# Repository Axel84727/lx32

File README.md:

# lx32

I built a computer from scratch because ChatGPT told me "no hay huevos." So here we are.

Custom processor, custom PCB, custom compiler. The whole thing.

---

## ok first let me flex

Zero violations. Zero unconnected items. I cried a little.

(also this is the 5th time I rewrote this README. if it still looks AI-generated I give up)

---

## what is this actually

lx32 is a 32-bit CPU with a custom instruction set, running on a custom PCB, compiled by a custom LLVM backend. You can write C, compile it, and it runs on this thing.

I wanted to actually understand how computers work, not just read about it. So I built one.

The board is 80x60mm, about the size of a credit card. Black soldermask, gold finish.

---

## the board

Here's what it looks like:

The schematics:

Measurements:

Long:

Width:

Full view:

The main chip is a Lattice iCE40HX4K FPGA — that's what becomes the processor. I chose it because the toolchain is fully open source (Yosys, nextpnr, icepack).

The rest of the board is USB-C for power and programming, SPI flash so the bitstream loads on power-up, two LDOs for the separate 3.3V and 1.2V rails, a USB-UART bridge to talk to it from my laptop, 32KB of external SRAM, and a VGA header. There's also an OLED that shows register values and the current instruction live, which is the coolest part honestly.

3D render, front:

3D render, back:

`.STEP` file if you want it: [`lx32-fpga.step`](./cad/lx32-fpga.step)

---

## the processor

32 registers, fixed 32-bit instruction width, single-cycle. I made up the instruction encoding: ADD, SUB, AND, OR, XOR, shifts, loads, stores, branches, jumps, LUI, AUIPC. x0 is hardwired to zero. Everything is in `rtl/` and every module has a spec in `docs/rtl/`.

---

## how I know it works

I wrote a Rust model of the processor, then a fuzzer that fires random instruction sequences through both Verilator and the model at the same time and compares cycle by cycle.

| module | test vectors | result |
|---|---|---|
| ALU | 100,000,000 | passed |
| Branch Unit | 100,000,000 | passed |
| Control Unit | 100,000,000 | passed |
| Register File | 100,000,000 | passed |
| Full System | 100,000,000 | passed |
| **Total** | **1,100,000,000+** | **zero failures** |

Runs in under 75 seconds. I also tortured my laptop with a Python script to run it on loop. There are Coq proofs for some properties and formal verification through sby too.

---

## the compiler

LLVM backend for lx32 — instruction patterns, register file, calling convention. Eight programs compile and run end-to-end: return, pointer store, call chain, branch/loop, compare/assign, pointer walk, iterative fibonacci, recursive fibonacci.

Write C, compile with LLVM, runs on this board.

---

## the gold art

ENIG means the exposed copper comes out gold on black soldermask. I put personal stuff on both sides.

The back has an infinity symbol, *pototo ralora arerita*, *"All we need is love"*, `Lizzie <3`, `22/03/09`, and `67` (that last one I didn't choose, it just ended up there).

It's a working computer and it also has my whole heart on it.

---

## run it yourself

```bash
git clone https://github.com/Axel84727/lx32.git
cd lx32
make setup
```

You'll need: `verilator`, Rust (`cargo`), `coqc`, `sby`, `yosys`, `z3`, `g++`.

```bash
make sim TB=lx32_system_tb    # full system sim
make validate                  # full test suite (1.1B vectors)
make formal-all                # formal proofs
```

---

## BOM

Full BOM: [`lx32-bom.csv`](./lx32-bom.csv)

| Part | Qty | Total |
| :--- | :---: | ---: |
| Custom LX32 PCB (JLCPCB, 4-layer, ENIG, black mask) | 5 | $15.00 |
| Lattice iCE40HX4K-TQ144 | 2 | $19.00 |
| CH340C USB-UART (SOP-16) | 2 | $0.90 |
| W25Q32JVSSIQ SPI Flash 32Mb | 2 | $1.10 |
| AP2112K-3.3TRG1 LDO 3.3V | 2 | $0.60 |
| AP2112K-1.2TRG1 LDO 1.2V | 2 | $0.60 |
| 25MHz Crystal SMD 3225 | 2 | $0.70 |
| USB-C connector SMD | 2 | $0.80 |
| Microchip 23K256 SPI SRAM (SOIC-8) | 2 | $1.20 |
| VGA 2x5 header + 68Ω resistors | -- | $0.76 |
| Passives (caps, resistors, LEDs) | -- | $0.58 |
| 2.54mm pin headers | 1 | $0.80 |
| M3 standoffs + screws | 12 | $1.00 |
| 0.96" OLED display | 1 | $14.22 |
| Jumper wires + breadboard | 1 | $9.89 |
| Shipping JLCPCB to Uruguay | -- | $22.00 |
| Shipping Tiendamia | -- | $38.00 |
| **Total** | | **$127.15** |

---

MIT

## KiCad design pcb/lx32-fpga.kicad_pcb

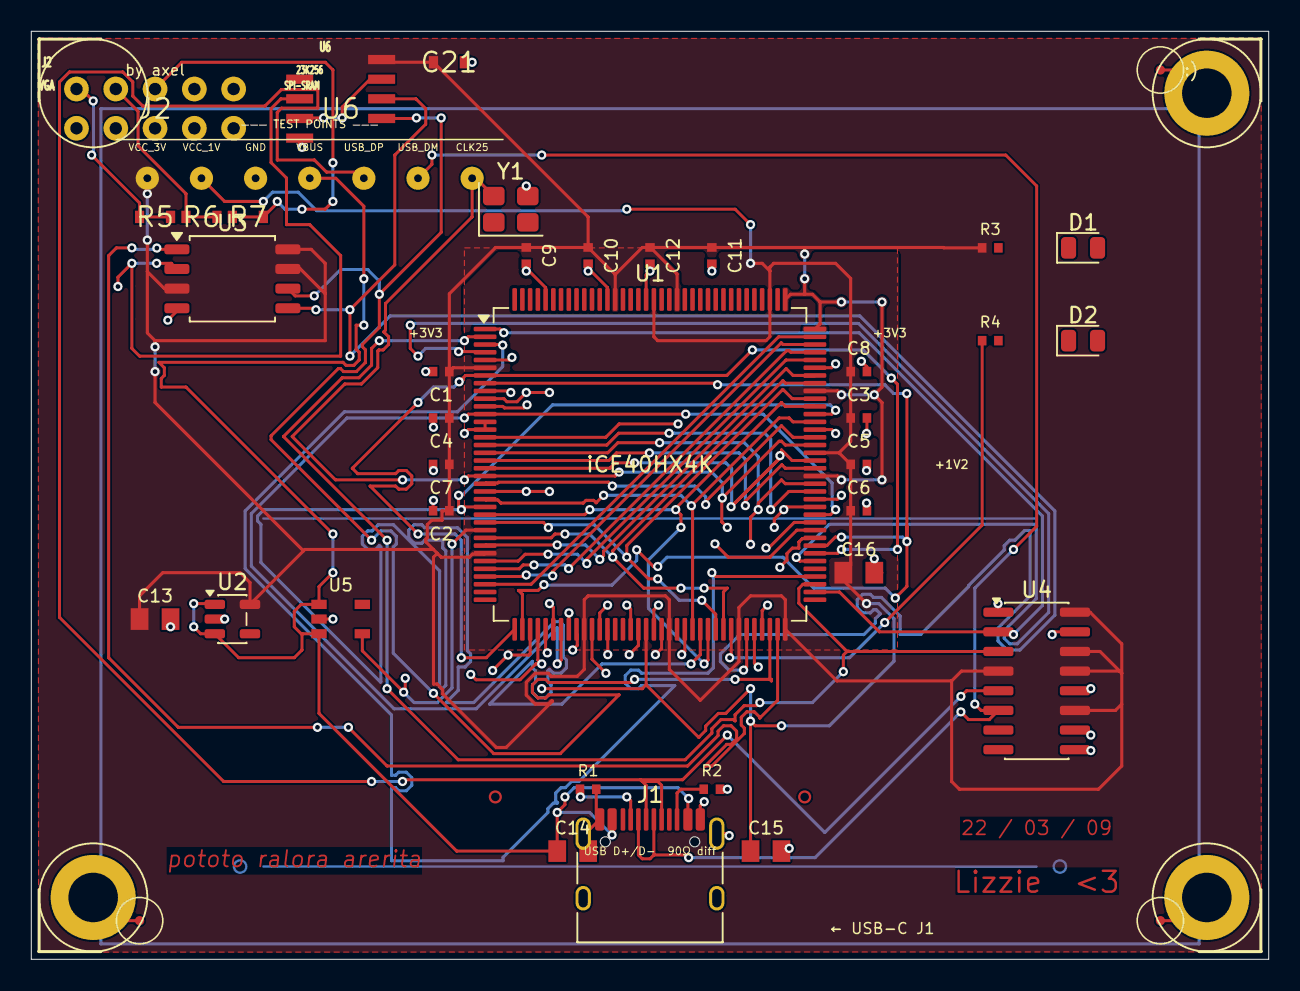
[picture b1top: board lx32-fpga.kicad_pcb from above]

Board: 4 copper layers, 80.0 x 60.0 mm, 49 parts (0 on the bottom side), 45 nets.

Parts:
C1, C2, C3, C4, C5, C6, C7, C8, C9, C10, C11, C12: 100nF; C_0402_1005Metric
C13, C14, C15, C16: 10uF; C_0805_2012Metric
C21: 100nF
D1, D2: LED; LED_0805_2012Metric
FID1, FID2, FID3: Fiducial
J1: USB_C_Receptacle_USB2.0_14P; USB_C_Receptacle
J2: VGA_HDR
MH1, MH2, MH3, MH4: MH_M3
R1, R2: 5.1k; R_0402_1005Metric
R3, R4: 100R; R_0402_1005Metric
R5, R6, R7: 68R
TP1: VCC_3V3
TP2: VCC_1V2
TP3: GND
TP4: VBUS
TP5: USB_DP
TP6: USB_DM
TP7: CLK25
U1: ICE40HX4K-TQ144; TQFP-144_20x20mm_P0.5mm
U2: AP2112K-3.3; SOT-23-5
U3: W25Q32JVSS; SOIC-8_5.3x5.3mm_P1.27mm
U4: CH340C; SOIC-16_3.9x9.9mm_P1.27mm
U5: AP2112K-1.2; SOT-23-5
U6: 23K256
Y1: Crystal; Crystal_SMD_3225-4Pin

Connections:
CC1: J1.A5 (CC1), R1.1
CC2: J1.B5 (CC2), R2.1
CDONE: R4.1, U1.65 (CDONE)
CLK25: TP7.1, U1.20 (IOL_13B_GBIN7), U1.52 (IOB_82_GBIN4), U1.93 (IOR_140_GBIN3), Y1.4
GND: C1.2, C2.2, C3.2, C4.2, C5.2, C6.2, C7.2, C8.2, C9.2, C10.2, C11.2, C12.2, C13.2, C14.2, C15.2, C16.2, C21.2, FID1.1, FID2.1, J1.A1 (GND), J1.A12 (GND), J1.B1 (GND), J1.B12 (GND), J1.SH (SHIELD), J2.6, J2.7, J2.8, J2.9, J2.10, MH2.1, MH3.1, MH4.1, R1.2, R2.2, TP3.1, U1.5 (GND), U1.13 (GND), U1.14 (GND), U1.53 (GNDPLL0), U1.59 (GND), U1.69 (GND), U1.86 (GND), U1.103 (GND), U1.127 (GNDPLL1), U1.132 (GND), U1.140 (GND), U2.2 (GND), U3.4 (GND), U4.1 (GND), U4.9 (~CTS), U4.10 (~DSR), U4.12 (~DCD), U4.15 (R232), U5.2, U6.4, Y1.3
unnamed: U1.3 (IOL_3A), U1.76 (IOR_112)
unnamed: U1.4 (IOL_3B), U1.78 (IOR_114)
unnamed: U1.7 (IOL_4A), U1.37 (IOB_56), U1.79 (IOR_115)
unnamed: U1.8 (IOL_4B), U1.38 (IOB_57), U1.80 (IOR_116)
unnamed: U1.9 (IOL_5A), U1.39 (IOB_61), U1.81 (IOR_117)
unnamed: U1.10 (IOL_5B), U1.41 (IOB_63), U1.82 (IOR_118)
unnamed: U1.11 (IOL_8A), U1.42 (IOB_64), U1.83 (IOR_119)
unnamed: U1.12 (IOL_8B), U1.43 (IOB_71), U1.84 (IOR_120)
unnamed: U1.15 (IOL_10A), U1.44 (IOB_72), U1.85 (IOR_128)
unnamed: U1.16 (IOL_10B), U1.45 (IOB_73), U1.87 (IOR_136)
unnamed: U1.17 (IOL_12A), U1.47 (IOB_79), U1.88 (IOR_137)
unnamed: U1.18 (IOL_12B), U1.48 (IOB_80), U1.90 (IOR_138)
unnamed: U1.19 (IOL_13A), U1.49 (IOB_81_GBIN5), U1.91 (IOR_139)
unnamed: U1.21 (IOL_14A_GBIN6), U1.55 (IOB_91), U1.94 (IOR_141_GBIN2)
unnamed: U1.22 (IOL_14B), U1.56 (IOB_94), U1.95 (IOR_144)
unnamed: U1.23 (IOL_17A), U1.60 (IOB_95), U1.96 (IOR_146)
unnamed: U1.24 (IOL_17B), U1.61 (IOB_96), U1.97 (IOR_147)
unnamed: U1.25 (IOL_18A), U1.62 (IOB_102), U1.98 (IOR_148)
unnamed: U1.26 (IOL_18B), U1.63 (IOB_103_CBSEL0), U1.99 (IOR_152)
unnamed: U1.28 (IOL_23A), U1.64 (IOB_104_CBSEL1), U1.101 (IOR_160)
unnamed: U1.29 (IOL_23B), U1.102 (IOR_161)
unnamed: U1.31 (IOL_24A), U1.104 (IOR_164)
unnamed: U1.32 (IOL_24B), U1.105 (IOR_165)
unnamed: U1.33 (IOL_25A), U1.106 (IOR_166)
unnamed: U1.34 (IOL_25B), U1.107 (IOR_167)
SPI_CLK: U1.70 (IOB_107_SCK), U3.6 (CLK), U6.5
SPI_MISO: U1.68 (IOB_106_SDI), U3.2 (DO/IO_{1}), U6.2
SPI_MOSI: U1.67 (IOB_105_SDO), U3.5 (DI/IO_{0}), U6.6
SPI_SS: U1.71 (IOB_108_SS), U3.1 (~CS)
SRAM_HOLD: U6.3, U6.7
UART_RX: U1.2 (IOL_2B), U1.75 (IOR_111), U4.3 (RXD)
UART_TX: U1.1 (IOL_2A), U1.74 (IOR_110), U4.2 (TXD)
USB_DM: J1.A7 (D-), J1.B7 (D-), TP6.1, U4.6 (UD-)
USB_DP: J1.A6 (D+), J1.B6 (D+), TP5.1, U4.5 (UD+)
VBUS: C14.1, J1.A4 (VBUS), J1.A9 (VBUS), J1.B4 (VBUS), J1.B9 (VBUS), TP4.1, U2.1 (VIN), U2.3 (EN), U5.1, U5.3
VCC_1V2: C3.1, C5.1, C6.1, C8.1, C15.1, C16.1, TP2.1, U1.27 (VCC), U1.40 (VCC), U1.54 (VCCPLL0), U1.92 (VCC), U1.111 (VCC), U1.126 (VCCPLL1), U5.5
VCC_3V3: C1.1, C2.1, C4.1, C7.1, C9.1, C10.1, C11.1, C12.1, C13.1, C21.1, R3.1, TP1.1, U1.6 (VCCIO_3), U1.30 (VCCIO_3), U1.46 (VCCIO_2), U1.57 (VCCIO_2), U1.66 (~CRESET), U1.72 (VCC_SPI), U1.89 (VCCIO_1), U1.100 (VCCIO_1), U1.108 (VPP_2V5), U1.109 (VPP_FAST), U1.123 (VCCIO_0), U1.131 (VCCIO_0), U2.5 (VOUT), U3.3 (~WP/IO_{2}), U3.7 (~HOLD/~RESET/IO_{3}), U3.8 (VCC), U4.4 (V3), U4.11 (~RI), U4.13 (~DTR), U4.14 (~RTS), U4.16 (VCC), U6.8
VGA_B: J2.3, R7.1, R7.2
VGA_G: J2.2, R6.1, R6.2
VGA_R: J2.1, R5.1, R5.2

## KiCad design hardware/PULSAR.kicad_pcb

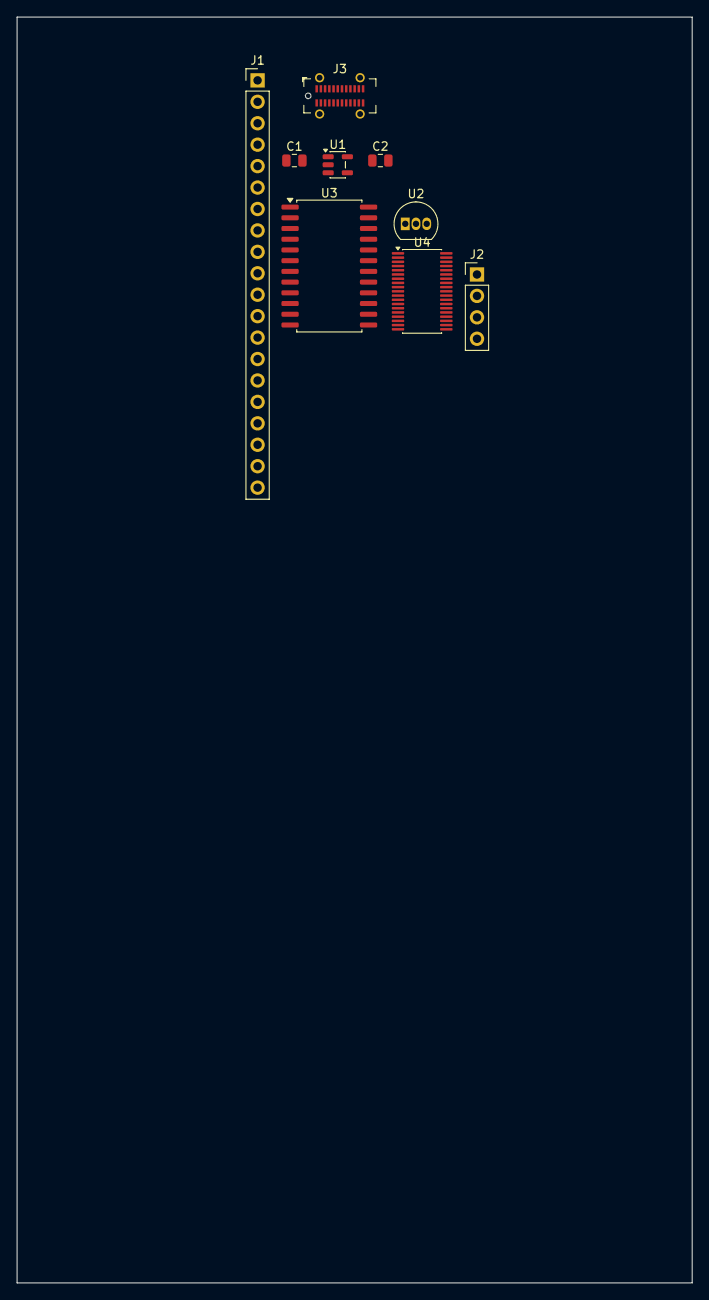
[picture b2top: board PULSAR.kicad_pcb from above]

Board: 4 copper layers, 80.0 x 150.0 mm, 9 parts (0 on the bottom side), 15 nets, no tracks yet.

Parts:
C1, C2: 1uF; C_0805_2012Metric
J1: Conn_01x20; PinHeader_1x20_P2.54mm_Vertical
J2: Conn_01x04; PinHeader_1x04_P2.54mm_Vertical
J3: USB_C_Receptacle; USB_C_Receptacle_GCT_USB4115-03-C
U1: AP2112K-3.3; SOT-23-5
U2: SS49E; TO-92_Inline
U3: CD74HC4067M; SOIC-24W_7.5x15.4mm_P1.27mm
U4: ADS8688; TSSOP-38_4.4x9.7mm_P0.5mm

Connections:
+3.3V: C2.1, J1.1, J2.1, U1.5 (VOUT), U2.1, U3.24 (VCC), U4.2 (~RST/PD), U4.4 (~REFSEL), U4.9 (AVDD), U4.30 (AVDD), U4.34 (DVDD)
+5V: C1.1, J3.A4 (VBUS), J3.A9 (VBUS), J3.B4 (VBUS), J3.B9 (VBUS), U1.1 (VIN), U1.3 (EN)
/HALL_OUT_1: U2.3, U3.9 (I0)
/MUX_OUT: J1.11, U3.1 (COM), U4.16 (AIN_0P)
/MUX_S0: J1.7, U3.10 (S0)
/MUX_S1: J1.8, U3.11 (S1)
/MUX_S2: J1.9, U3.14 (S2)
/MUX_S3: J1.10, U3.13 (S3)
/SPI_CS1: J1.6, U4.38 (~CS)
/SPI_SCLK: J1.5, U4.37 (SCLK)
/SPI_SDI: J1.4, U4.1 (SDI)
/SPI_SDO: J1.3, U4.36 (SDO)
/USB_DN: J3.A7 (D-), J3.B7 (D-)
/USB_DP: J3.A6 (D+), J3.B6 (D+)
GND: C1.2, C2.2, J1.2, J2.2, J3.A1 (GND), J3.A12 (GND), J3.B1 (GND), J3.B12 (GND), U1.2 (GND), U2.2, U3.12 (GND), U3.15 (~E), U4.5 (REFIO), U4.6 (REFGND), U4.7 (REFCAP), U4.8 (AGND), U4.11 (AUX_GND), U4.13 (AIN_6GND), U4.15 (AIN_7GND), U4.17 (AIN_0GND), U4.19 (AIN_1GND), U4.20 (AIN_2GND), U4.22 (AIN_3GND), U4.24 (AIN_4GND), U4.26 (AIN_5GND), U4.28 (AGND), U4.29 (AGND), U4.31 (AGND), U4.32 (AGND), U4.33 (DGND)

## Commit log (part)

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2026-02-06 Update README with project details and objectives
    Expanded project description and outlined goals, non-goals, and scope.
2026-02-06 feat: add basic testbench for reg1
2026-02-08 feat: add initial RTL structure and parametrized generic register
2026-02-08 feat(core): implement 32-bit RISC-V style register file
    - Add 31x32-bit generic register instantiation
    - Implement zero-register (x0) hardwired to constant zero
    - Add dual-read and single-write ports logic
    - Include comprehensive testbench for verification
2026-02-09 feat(branch): define branch operation encodings
2026-02-09 feat(alu): implement integer ALU with branch comparison support
2026-02-09 feat: wrap alu opcodes in package and drop unused all package
2026-02-09 fix: duplicate package inclusion in Makefile
2026-02-10 feat(tb): add testbench for immediate generator validation
2026-02-10 fix(imm): silence iverilog always_comb warnings
2026-02-11 feat(core): implement control unit with main and alu decoders
2026-02-25 feat(core): integrate modules into lx32_core and verify with system tb
    Connects ALU, RegFile, ControlUnit, and LSU. Verified successful 32-bit addition and branching in simulation.
2026-02-25 fix(rtl): remove Icarus Verilog constant select and memory init warnings in alu and memory_sim modules
    - Move all constant select (bit slicing) assignments outside always blocks using continuous assign for Icarus compatibility
    - Initialize RAM to zero before $readmemh in memory_sim to suppress 'Not enough words' warning
    - No functional changes, only simulation compatibility improvements
2026-02-25 test: add memory-mapped I/O monitor to system testbench
2026-02-28 Add GitHub Actions workflow for Rust project
2026-02-28 Add lint target for RTL simulation checks
    Add lint target to Makefile for RTL linting checks.
2026-02-28 Rename CI workflow and update steps for Verilator (#16)
    Updated CI workflow to focus on Hardware CI with Verilator installation and linting.
2026-02-28 Specify top module in lint target (#17)
    Updated lint target to specify top module for Verilator.
2026-02-28 feat: implemented branch operation encoding
2026-02-28 feat: implemented alu logic in rust-golden-model
2026-02-28 feat: implemented immediate generation unit rust - G.M
2026-02-28 feat: implemented simulation memory rust - G.M
2026-02-28 feat: list the both directories
2026-02-28 quick commit to use codespaces
2026-03-01 refactor: made better test for alu & branch unit
2026-03-01 tests: added test for imm_gen module
2026-03-01 tests: added test for memory_sim module
2026-03-01 tests: added test for lx32_system module
2026-03-01 Add test-all-testbenches job to GitHub Actions
2026-03-01 Refactor GitHub Actions workflow for Rust testing
2026-03-01 Change CI workflow from Verilator to Rust tests
    Updated CI workflow to run Rust tests instead of Verilator tests.
2026-03-01 Update Rust CI to specify manifest path for build and run
2026-03-01 Update Makefile (#25)
2026-03-01 Update GitHub Actions workflow for Rust project (#26)
2026-03-01 Remove duplicate .sim directory creation step
2026-03-01 Create simulation library directory in Makefile (#29)
    Add command to create simulation library directory before generating C++ files.
2026-03-01 Update Makefile (#31)
2026-03-01 Enhance build step with directory permissions
    Added permissions adjustment for .sim directory before building the RTL library.
2026-03-01 Refactor Rust CI workflow for RTL generation and testing
    Updated GitHub Actions workflow to streamline RTL generation and build process.
2026-03-01 Update Makefile for Verilator portability and paths
2026-03-01 Enhance Verilator root detection and comments
    Updated Verilator root detection for macOS and Linux, added comments for clarity, and ensured compatibility with various environments.
2026-03-01 Refactor Verilator installation steps in workflow
2026-03-01 Add comment for CI test in build.rs
2026-03-01 Rename steps in Rust CI workflow for clarity
2026-03-01 Update Rust CI workflow with improved steps and naming
2026-03-01 Add verification and robustness section to README
    Added verification section detailing stress testing results.
2026-03-08 feat: Add advanced_validation.md documenting reproducible seeds, long program generation, and automatic shrinking for validator
2026-03-08 chore: add clap dependency with derive feature to Cargo.toml
2026-03-08 feat: add program_generator and shrinking modules to lib.rs exports
2026-03-08 feat: add CLI argument parsing and seed control to main.rs for flexible test orchestration
2026-03-08 feat: add current_instr and current_mem_rdata fields to TestBench and implement helper functions for long program tests
2026-03-08 style: add blank lines to register_file.rs for improved readability
2026-03-08 feat: add test_runner.rs module to orchestrate execution of validation test suites based on configuration
2026-03-08 docs: add validator_quickstart.md with instructions for setup, usage, CI integration, and troubleshooting
2026-03-08 feat: add automated setup script and silence validator warnings (#54)
2026-03-08 ci: migrate rust workflow to use 'make setup'
2026-03-08 Update .gitignore to exclude .idea directory
2026-03-08 docs: add alu.md documenting RTL ALU design, interface, and integration
2026-03-08 docs: add bridge.md documenting hardware bridge design, interface, and integration
2026-03-08 docs: add control_unit.md documenting golden model control unit design, interface, and integration
2026-03-08 docs: add generic_template_arch.md documenting golden model architecture package design, structure, and integration
2026-03-08 docs: add generic_template_src.md documenting source module design, interface, and integration
2026-03-08 docs: add imm_gen.md documenting RTL immediate generation module design, interface, structure, and integration
2026-03-08 docs: add lsu.md documenting RTL load/store unit design, interface, structure, and integration
2026-03-08 docs: add lx32_arch_pkg.md documenting golden model architecture package types, constants, and integration
2026-03-08 docs: add lx32_branch_pkg.md documenting RTL branch package enums, constants, and integration
2026-03-08 docs: add lx32_decode_pkg.md documenting RTL decode package constants, types, and integration
2026-03-08 docs: add lx32_system.md documenting RTL core module integration, interfaces, and pipeline stages
2026-03-08 docs: add memory_sim.md documenting RTL simulation memory model design, interface, and integration
2026-03-08 docs: add mod.md documenting common utilities module structure, interfaces, and integration
2026-03-08 docs: add README.md providing comprehensive guide and deep reference for LX32 documentation structure, module relationships, and integration workflow
2026-03-08 docs: add register_file.md documenting golden model register file design, interfaces, validation, and integration
2026-03-08 docs: add shrinking.md documenting LX32 test case shrinker design, strategies, interfaces, and integration
2026-03-08 docs: add test_control_unit.md documenting control unit test module design, parameters, flow, and integration for LX32 core
2026-03-08 docs: add test_long_programs.md documenting long programs test module design, parameters, flow, and integration for LX32 core
2026-03-08 docs: add test_reg_generic.md documenting generic register test module design, parameters, flow, and integration for LX32 core
2026-03-08 docs: add generic core module documentation templates and validator Makefile usage guide
2026-03-17 Enhance README with project overview and objectives
    Expanded project description to clarify goals and approach.
2026-03-24 Refactor: LX32.td
2026-03-24 style(lx32): finalize target definition and fix merge conflicts
2026-03-24 feat(backend): implement LX32 MCTargetDesc foundation
    - Add LX32MCAsmInfo with ELF-only support
    - Add LX32MCTargetDesc with target MC registration
    - Register MCAsmInfo, MCInstrInfo, MCRegInfo, MCSubtargetInfo
    - Add mc/ CMakeLists.txt and connect to build
    - Compiles cleanly: libLLVMLX32Desc.a
2026-03-24 feat(backend): implement LX32RegisterInfo.td
    - Define LX32Reg class with hardware encoding and ABI alt names
    - Register x0-x31 with full ABI naming (zero, ra, sp, gp, tp, t0-t6, s0-s11, a0-a7, fp)
    - Define ABIRegAltName index
    - Define GPR and GPRNOX0 register classes based on lx-Ω ABI
    - Verified with llvm-tblgen --print-records
2026-03-25 Feat/llvm backend (#71)
    * feat: added support for llvm-backend in makefile
    * feat: added Triple in llvm backend
    * feat(backend): add LX32 LLVM backend scaffold
    - Register LX32 as experimental target in Triple
    - Add LX32 data layout in TargetDataLayout
    - Implement LX32TargetInfo with target registration
2026-04-01 Remove LX32 instruction definitions
2026-04-02 feat: reorganize CMakeLists to streamline target structure
2026-04-02 feat: enhance LX32InstrInfo.h with comprehensive documentation and structure
2026-04-02 feat: enhance LX32MCAsmInfo.cpp with detailed documentation and constructor defaults
2026-04-02 feat: enhance LX32MCTargetDesc.h with detailed documentation and section organization
2026-04-02 feat: enhance LX32Subtarget.h with structured documentation and section organization
2026-04-02 feat: enhance LX32TargetMachine.cpp with structured documentation and section organization
2026-04-02 feat: add CMakeLists.txt for LX32 CodeGen layer
2026-04-04 refactor: delete .inc files from commit
2026-04-05 chore: commit remaining rtl, tb, validator, and ci updates
    - include remaining workflow and ignore-file adjustments\n- include rtl/core and tb/core updates from cleanup/debug pass\n- include validator model and test updates\n- include validator usage doc ref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
2026-04-06 Refactor LLVM LX32 backend structure, fix C baremetal compiling, and update docs
2026-04-06 fix(lx32-backend): support unconditional branch selection
2026-04-06 Fix: correct fixup creation, ELF relocation mapping, and Makefile for CI and backend correctness
2026-04-08 lx32: fix branch pseudo expansion and call clobber modeling (#85)
2026-04-09 chore: add @AgusVeega to the codeowners file (#2)
2026-04-10 sync: import backend build + TableGen integration from Pulsar
2026-04-11 feat: assign footprints to all schematic components
2026-04-23 Add assembly generation script for FreeCAD
2026-04-23 Change image reference in README for CAD model (#92)
    Updated image reference for the hardware block model in the README.
2026-04-23 Update CAD export file path in README
2026-04-23 Add files via upload (#93)
2026-04-23 chore: changed the readme to meet hackclub requirements (#97)
2026-04-26 add custom FPGA carrier PCB — iCE40HX4K-TQ144, full KiCad design, gerbers, STEP (#99)
    Custom-designed 2-layer FPGA carrier board for lx32. Designed from scratch in
    KiCad around the Lattice iCE40HX4K-TQ144. This replaces the previously mentioned
    premade dev board approach — everything here is hand-designed.
    Board specs:
    - 80×60mm, 2-layer FR4, ENIG surface finish, black soldermask
    - iCE40HX4K-TQ144 (3.5K LUTs, 80KB BRAM) — enough headroom for lx32 single-cycle core
2026-04-26 Change image link format in README.md
    Updated image reference format in README.
2026-04-26 add custom FPGA carrier PCB — iCE40HX4K-TQ144, full KiCad design, gerbers, STEP (#102)
    Custom-designed 2-layer FPGA carrier board for lx32. Designed from scratch in
    KiCad around the Lattice iCE40HX4K-TQ144. This replaces the previously mentioned
    premade dev board approach — everything here is hand-designed.
    Board specs:
    - 80×60mm, 2-layer FR4, ENIG surface finish, black soldermask
    - iCE40HX4K-TQ144 (3.5K LUTs, 80KB BRAM) — enough headroom for lx32 single-cycle core
2026-05-02 [ImgBot] Optimize images
    *Total -- 3,178.53kb -> 1,705.28kb (46.35%)
    /pcb_front_3d.png -- 265.98kb -> 116.97kb (56.02%)
    /pcb_back_3d.png -- 216.65kb -> 99.19kb (54.22%)
    /pcb_long.png -- 480.47kb -> 256.31kb (46.65%)
    /pcb_first_look.png -- 650.92kb -> 349.50kb (46.31%)
    /pcb_width.png -- 598.01kb -> 325.08kb (45.64%)
2026-05-09 chore: changed the bom to match the csv with the readme (#105)
2026-05-14 Review/feedback (#106)
    * chore: changed the bom to match the csv with the readme
    * feat: added the png schematics
